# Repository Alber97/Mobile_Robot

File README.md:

# Mobile_Robot
Mobile robot, line follower, PID controller, joystick control

###
C/C++ code for stm32, eagle pcb project and MIT APP Inventor application for android systems

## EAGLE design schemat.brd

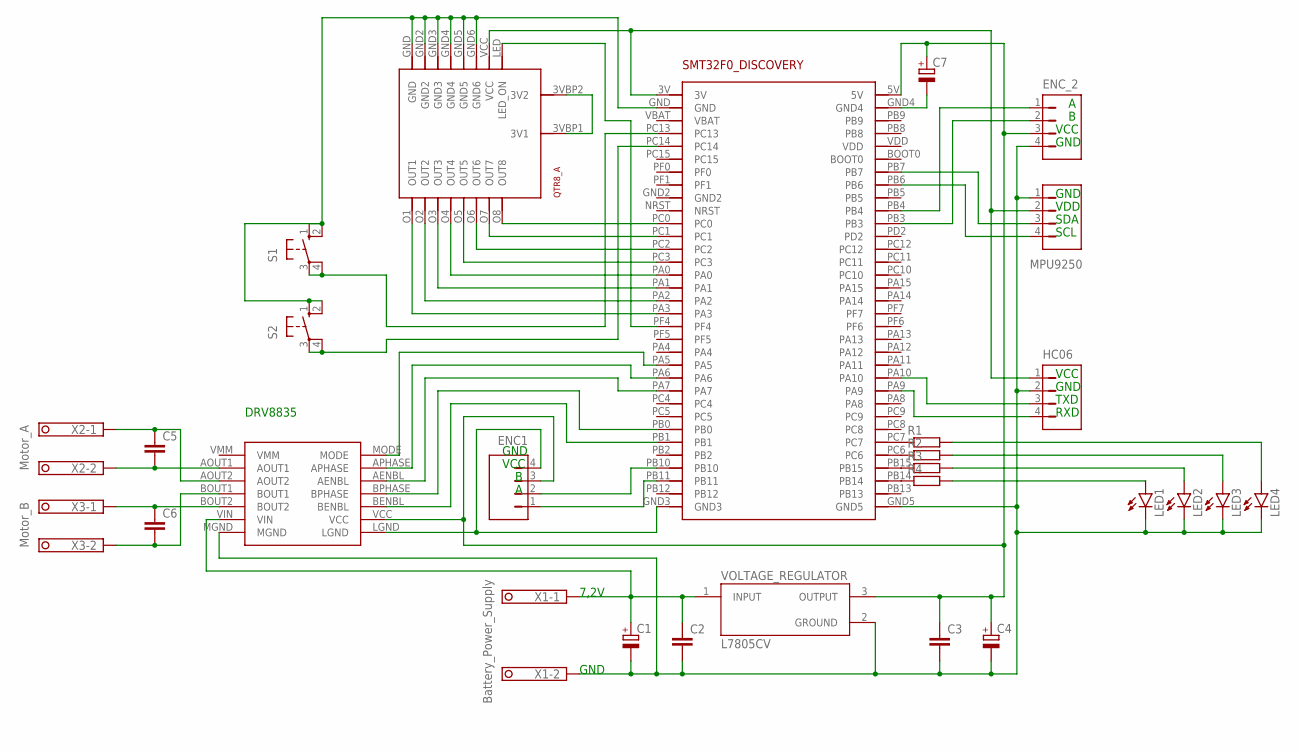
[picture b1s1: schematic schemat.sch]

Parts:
C1, C4, C7: CPOL-EUE2.5-6; E2,5-6
C2, C3, C5, C6: C-EU025-024X044; C025-024X044
DRV8835: POLOLU_MOTOR_DRV8835THROUGHHOLE; POLOLU_MOTOR_DRV_DRV8835
ENC1: JP4E; JP4
ENC_2: JP4E; JP4
HC06: JP4E; JP4
LED1, LED2, LED3, LED4: LEDB152; Q62902-B152
MPU9250: JP4E; JP4
R1, R2, R3, R4: R-EU_0207/7; 0207/7
S1, S2: 10-XX; B3F-10XX
SMT32F0_DISCOVERY: STM32F0_DISCOVERY
U$1: QTR8_A
VOLTAGE_REGULATOR: L7805CV; TO255P1040X460X1968-3
X1: Battery_Power_Supply; 1751248
X2: Motor_A; 1751248
X3: Motor_B; 1751248

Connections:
3V: HC06.1, MPU9250.2, SMT32F0_DISCOVERY.3V, U$1.VCC
5V: C3.1, C4.+, C7.+, DRV8835.VCC, ENC1.3, ENC_2.3, SMT32F0_DISCOVERY.5V, VOLTAGE_REGULATOR.3 (OUTPUT)
+7,2V: C1.+, C2.1, DRV8835.VIN, VOLTAGE_REGULATOR.1 (INPUT), X1.1
GND: C1.-, C2.2, C3.2, C4.-, DRV8835.MGND, ENC_2.4, HC06.2, LED1.K (C), LED2.K (C), LED3.K (C), LED4.K (C), MPU9250.1, SMT32F0_DISCOVERY.GND5, VOLTAGE_REGULATOR.2 (GROUND), X1.2
unnamed: C7.-, SMT32F0_DISCOVERY.GND4
unnamed: DRV8835.LGND, ENC1.4, SMT32F0_DISCOVERY.GND3
unnamed: C5.2, DRV8835.AOUT1, X2.2
unnamed: SMT32F0_DISCOVERY.PC0, U$1.O8 (OUT8)
unnamed: ENC1.2, SMT32F0_DISCOVERY.PB10
unnamed: R1.1, SMT32F0_DISCOVERY.PC7
unnamed: ENC1.1, SMT32F0_DISCOVERY.PB11
unnamed: SMT32F0_DISCOVERY.PA1, U$1.O3 (OUT3)
unnamed: U$1.3VBP1 (3V1), U$1.3VBP2 (3V2)
unnamed: HC06.3, SMT32F0_DISCOVERY.PA10
unnamed: HC06.4, SMT32F0_DISCOVERY.PA9
unnamed: MPU9250.3, SMT32F0_DISCOVERY.PB7
unnamed: MPU9250.4, SMT32F0_DISCOVERY.PB6
unnamed: SMT32F0_DISCOVERY.PA2, U$1.O2 (OUT2)
unnamed: SMT32F0_DISCOVERY.PA3, U$1.O1 (OUT1)
unnamed: DRV8835.BENBL, SMT32F0_DISCOVERY.PB1
unnamed: DRV8835.BPHASE, SMT32F0_DISCOVERY.PB0
unnamed: SMT32F0_DISCOVERY.PC1, U$1.O7 (OUT7)
unnamed: SMT32F0_DISCOVERY.PC2, U$1.O6 (OUT6)
unnamed: S1.3, S1.4 (P1), SMT32F0_DISCOVERY.PC13
unnamed: R2.1, SMT32F0_DISCOVERY.PC6
unnamed: C6.2, DRV8835.BOUT1, X3.2
unnamed: S1.1 (S), S1.2 (S1), S2.1 (S), S2.2 (S1), SMT32F0_DISCOVERY.GND, U$1.GND, U$1.GND2, U$1.GND3, U$1.GND4, U$1.GND5, U$1.GND6
unnamed: SMT32F0_DISCOVERY.PC3, U$1.O5 (OUT5)
unnamed: SMT32F0_DISCOVERY.PA0, U$1.O4 (OUT4)
unnamed: DRV8835.AENBL, SMT32F0_DISCOVERY.PA7
unnamed: DRV8835.APHASE, SMT32F0_DISCOVERY.PA6
unnamed: DRV8835.MODE, SMT32F0_DISCOVERY.PA5
unnamed: SMT32F0_DISCOVERY.PF4, U$1.LED (LED_ON)
unnamed: R3.1, SMT32F0_DISCOVERY.PB15
unnamed: ENC_2.2, SMT32F0_DISCOVERY.PB3
unnamed: ENC_2.1, SMT32F0_DISCOVERY.PB4
unnamed: R4.1, SMT32F0_DISCOVERY.PB14
unnamed: LED1.A, R4.2
unnamed: LED2.A, R3.2
unnamed: LED3.A, R2.2
unnamed: LED4.A, R1.2
unnamed: S2.3, S2.4 (P1), SMT32F0_DISCOVERY.PC14
unnamed: C5.1, DRV8835.AOUT2, X2.1
unnamed: C6.1, DRV8835.BOUT2, X3.1

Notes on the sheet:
DRV8835
GND
VDD
SDA
SCL
VCC
TXD
RXD
7,2V

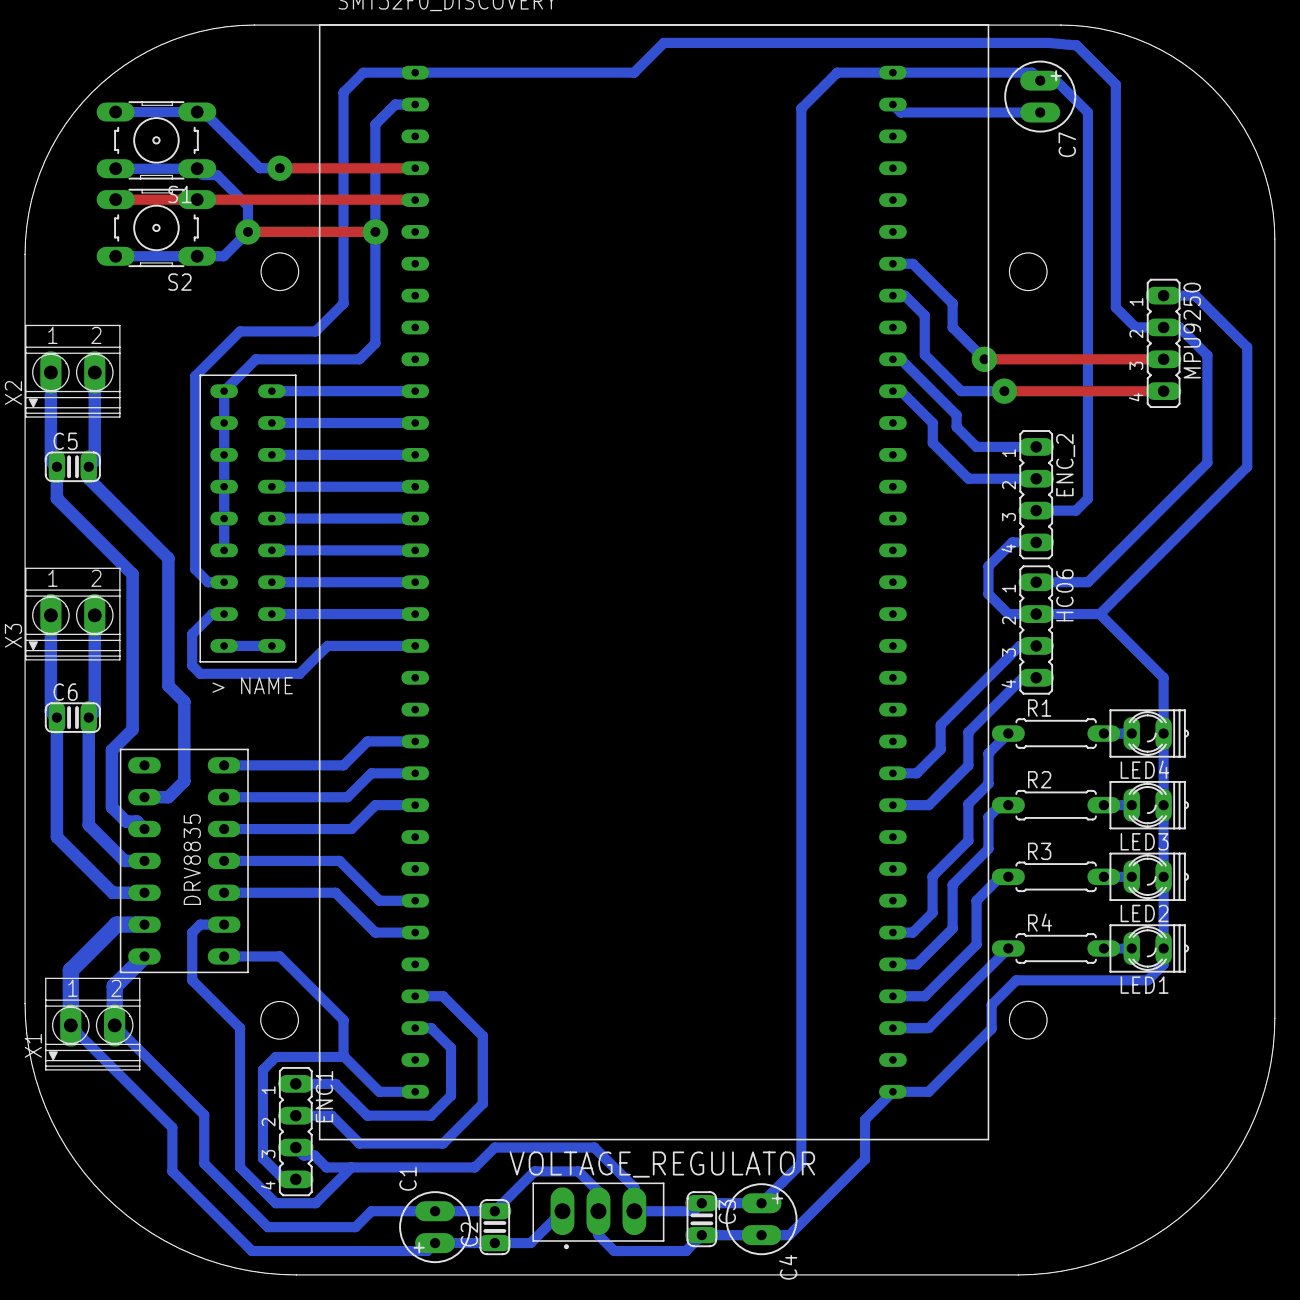
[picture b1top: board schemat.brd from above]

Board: 2 copper layers, 99.7 x 99.7 mm, 28 parts (0 on the bottom side), 44 nets.

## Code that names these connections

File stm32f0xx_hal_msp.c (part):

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    __HAL_RCC_GPIOC_CLK_ENABLE();
    __HAL_RCC_GPIOA_CLK_ENABLE();
    /**ADC GPIO Configuration    
    PC0     ------> ADC_IN10
    PC1     ------> ADC_IN11
    PC2     ------> ADC_IN12
    PC3     ------> ADC_IN13
    PA0     ------> ADC_IN0
    PA1     ------> ADC_IN1
    PA2     ------> ADC_IN2
    PA3     ------> ADC_IN3 
    */
    GPIO_InitStruct.Pin = GPIO_PIN_0|GPIO_PIN_1|GPIO_PIN_2|GPIO_PIN_3;
    GPIO_InitStruct.Mode = GPIO_MODE_ANALOG;
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    __HAL_RCC_ADC1_CLK_DISABLE();
  
    /**ADC GPIO Configuration    
    PC0     ------> ADC_IN10
    PC1     ------> ADC_IN11
    PC2     ------> ADC_IN12
    PC3     ------> ADC_IN13
    PA0     ------> ADC_IN0
    PA1     ------> ADC_IN1
    PA2     ------> ADC_IN2
    PA3     ------> ADC_IN3 
    */
    HAL_GPIO_DeInit(GPIOC, GPIO_PIN_0|GPIO_PIN_1|GPIO_PIN_2|GPIO_PIN_3);

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  
    __HAL_RCC_GPIOB_CLK_ENABLE();
    /**I2C1 GPIO Configuration    
    PB6     ------> I2C1_SCL
    PB7     ------> I2C1_SDA 
    */
    GPIO_InitStruct.Pin = GPIO_PIN_6|GPIO_PIN_7;
    GPIO_InitStruct.Mode = GPIO_MODE_AF_OD;
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    __HAL_RCC_I2C1_CLK_DISABLE();
  
    /**I2C1 GPIO Configuration    
    PB6     ------> I2C1_SCL
    PB7     ------> I2C1_SDA 
    */
    HAL_GPIO_DeInit(GPIOB, GPIO_PIN_6|GPIO_PIN_7);

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  
    __HAL_RCC_GPIOA_CLK_ENABLE();
    /**USART1 GPIO Configuration    
    PA9     ------> USART1_TX
    PA10     ------> USART1_RX 
    */
    GPIO_InitStruct.Pin = GPIO_PIN_9|GPIO_PIN_10;
    GPIO_InitStruct.Mode = GPIO_MODE_AF_PP;
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    __HAL_RCC_USART1_CLK_DISABLE();
  
    /**USART1 GPIO Configuration    
    PA9     ------> USART1_TX
    PA10     ------> USART1_RX 
    */
    HAL_GPIO_DeInit(GPIOA, GPIO_PIN_9|GPIO_PIN_10);

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

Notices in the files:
stm32f0xx_hal_msp.c:
© Copyright (c) 2020 STMicroelectronics.
All rights reserved.
This software component is licensed by ST under BSD 3-Clause license,
the "License"; You may not use this file except in compliance with the
License. You may obtain a copy of the License at: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
(C) COPYRIGHT STMicroelectronics *****END OF FILE
